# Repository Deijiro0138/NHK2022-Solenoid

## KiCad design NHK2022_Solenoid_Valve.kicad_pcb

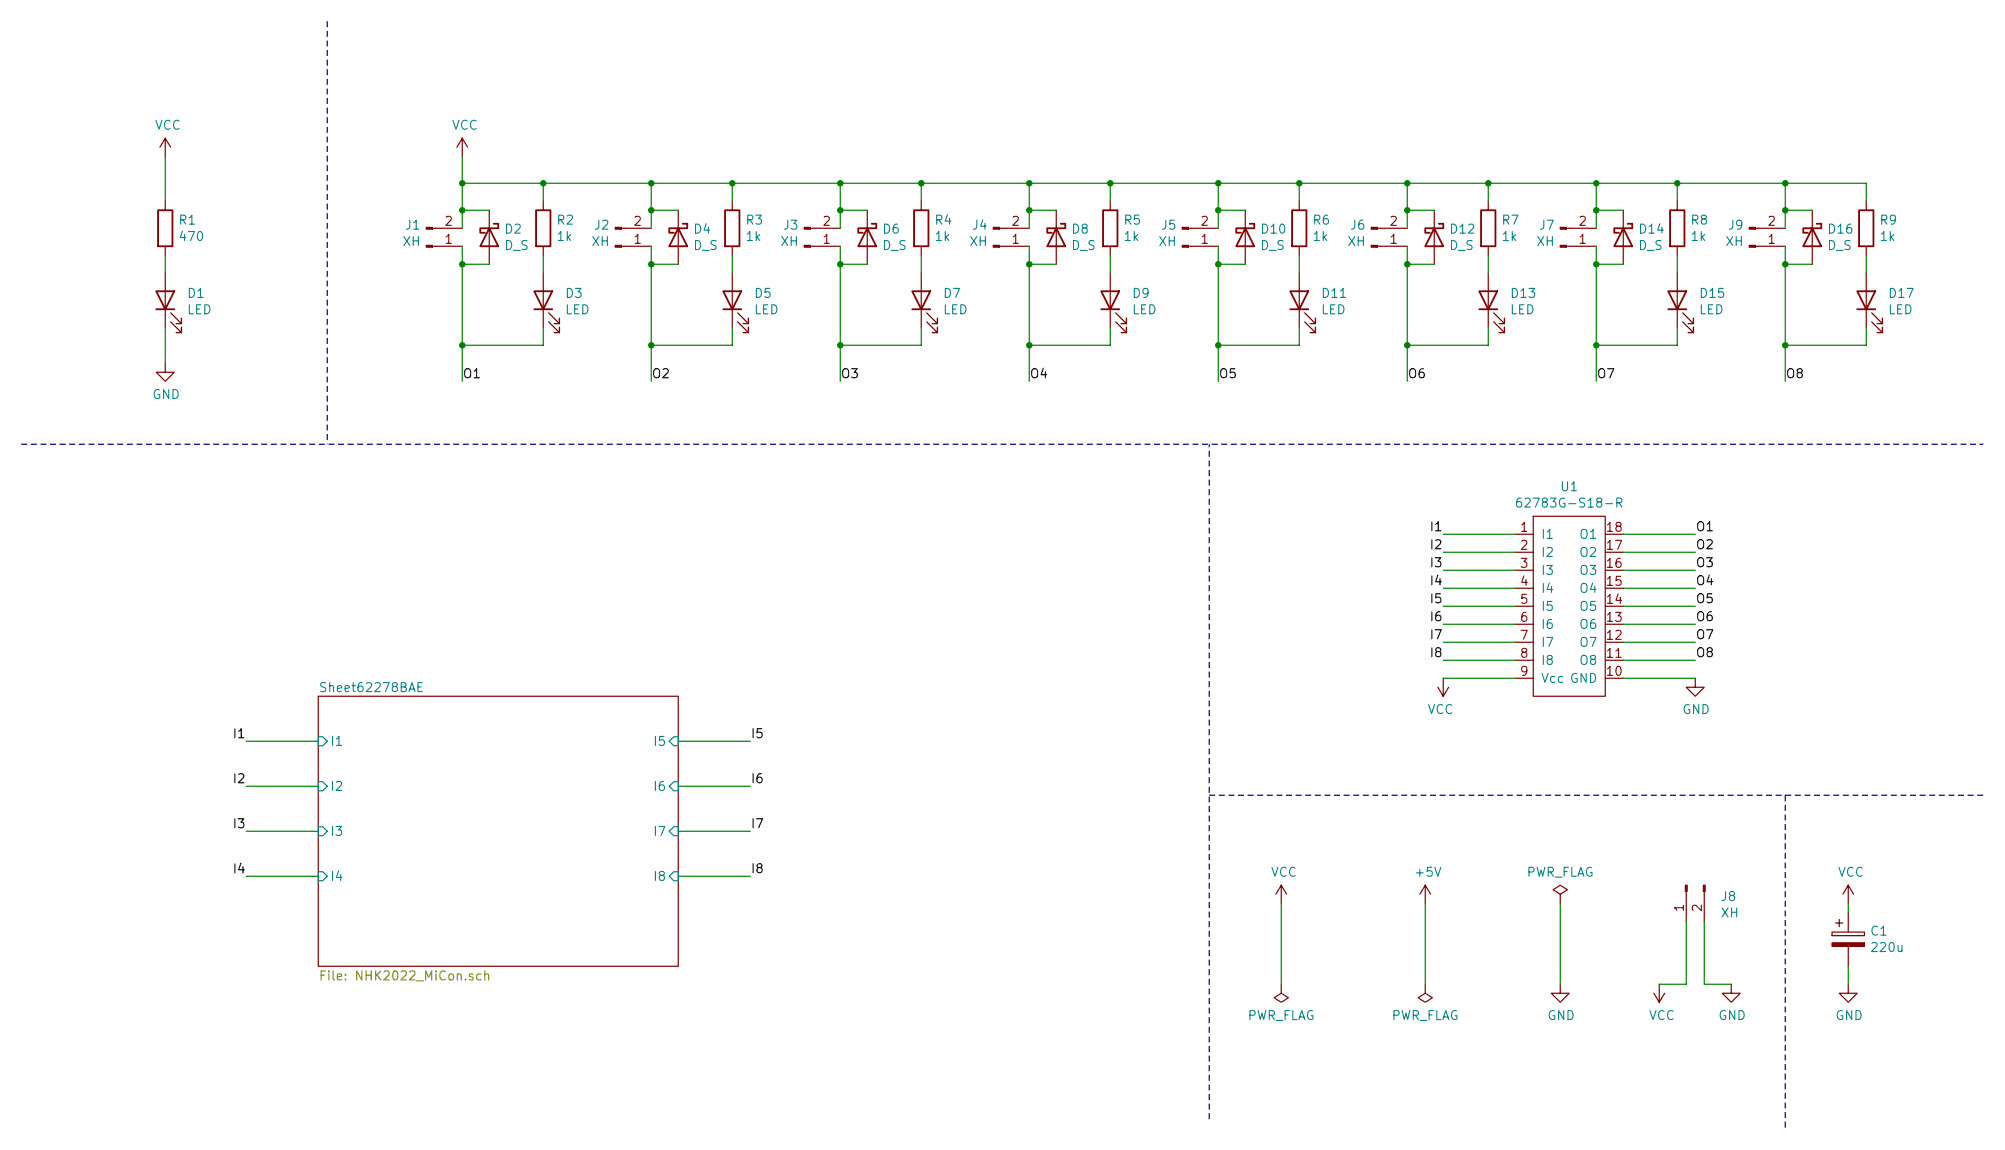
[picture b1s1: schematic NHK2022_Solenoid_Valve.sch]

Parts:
C1: 220u; CP_Radial_D8.0mm_P3.50mm
D1, D3, D5, D7, D9, D11, D13, D15, D17: LED; LED_0603_1608Metric
D2, D4, D6, D8, D10, D12, D14, D16: D_S; D_SOD-323_HandSoldering
J1, J2, J3, J4, J5, J6, J7, J8, J9: XH; JST_XH_S2B-XH-A_1x02_P2.50mm_Horizontal
R1: 470; R_0603_1608Metric
R2, R3, R4, R5, R6, R7, R8, R9: 1k; R_0603_1608Metric
U1: 62783G-S18-R; SOP-18_7x12.5mm_P1.27mm

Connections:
/I1: U1.1 (I1); also elsewhere on the board
/I2: U1.2 (I2); also elsewhere on the board
/I3: U1.3 (I3); also elsewhere on the board
/I4: U1.4 (I4); also elsewhere on the board
/I5: U1.5 (I5); also elsewhere on the board
/I6: U1.6 (I6); also elsewhere on the board
/I7: U1.7 (I7); also elsewhere on the board
/I8: U1.8 (I8); also elsewhere on the board
/O1: D2.2 (A), D3.1 (K), J1.1, U1.18 (O1)
/O2: D4.2 (A), D5.1 (K), J2.1, U1.17 (O2)
/O3: D6.2 (A), D7.1 (K), J3.1, U1.16 (O3)
/O4: D8.2 (A), D9.1 (K), J4.1, U1.15 (O4)
/O5: D10.2 (A), D11.1 (K), J5.1, U1.14 (O5)
/O6: D12.2 (A), D13.1 (K), J6.1, U1.13 (O6)
/O7: D14.2 (A), D15.1 (K), J7.1, U1.12 (O7)
/O8: D16.2 (A), D17.1 (K), J9.1, U1.11 (O8)
GND: C1.2, D1.1 (K), J8.2, U1.10 (GND); also elsewhere on the board
unnamed: D1.2 (A), R1.2
unnamed: D3.2 (A), R2.2
unnamed: D5.2 (A), R3.2
unnamed: D7.2 (A), R4.2
unnamed: D9.2 (A), R5.2
unnamed: D11.2 (A), R6.2
unnamed: D13.2 (A), R7.2
unnamed: D15.2 (A), R8.2
unnamed: D17.2 (A), R9.2
VCC: C1.1, D2.1 (K), D4.1 (K), D6.1 (K), D8.1 (K), D10.1 (K), D12.1 (K), D14.1 (K), D16.1 (K), J1.2, J2.2, J3.2, J4.2, J5.2, J6.2, J7.2, J8.1, J9.2, R1.1, R2.1, R3.1, R4.1, R5.1, R6.1, R7.1, R8.1, R9.1, U1.9 (Vcc)

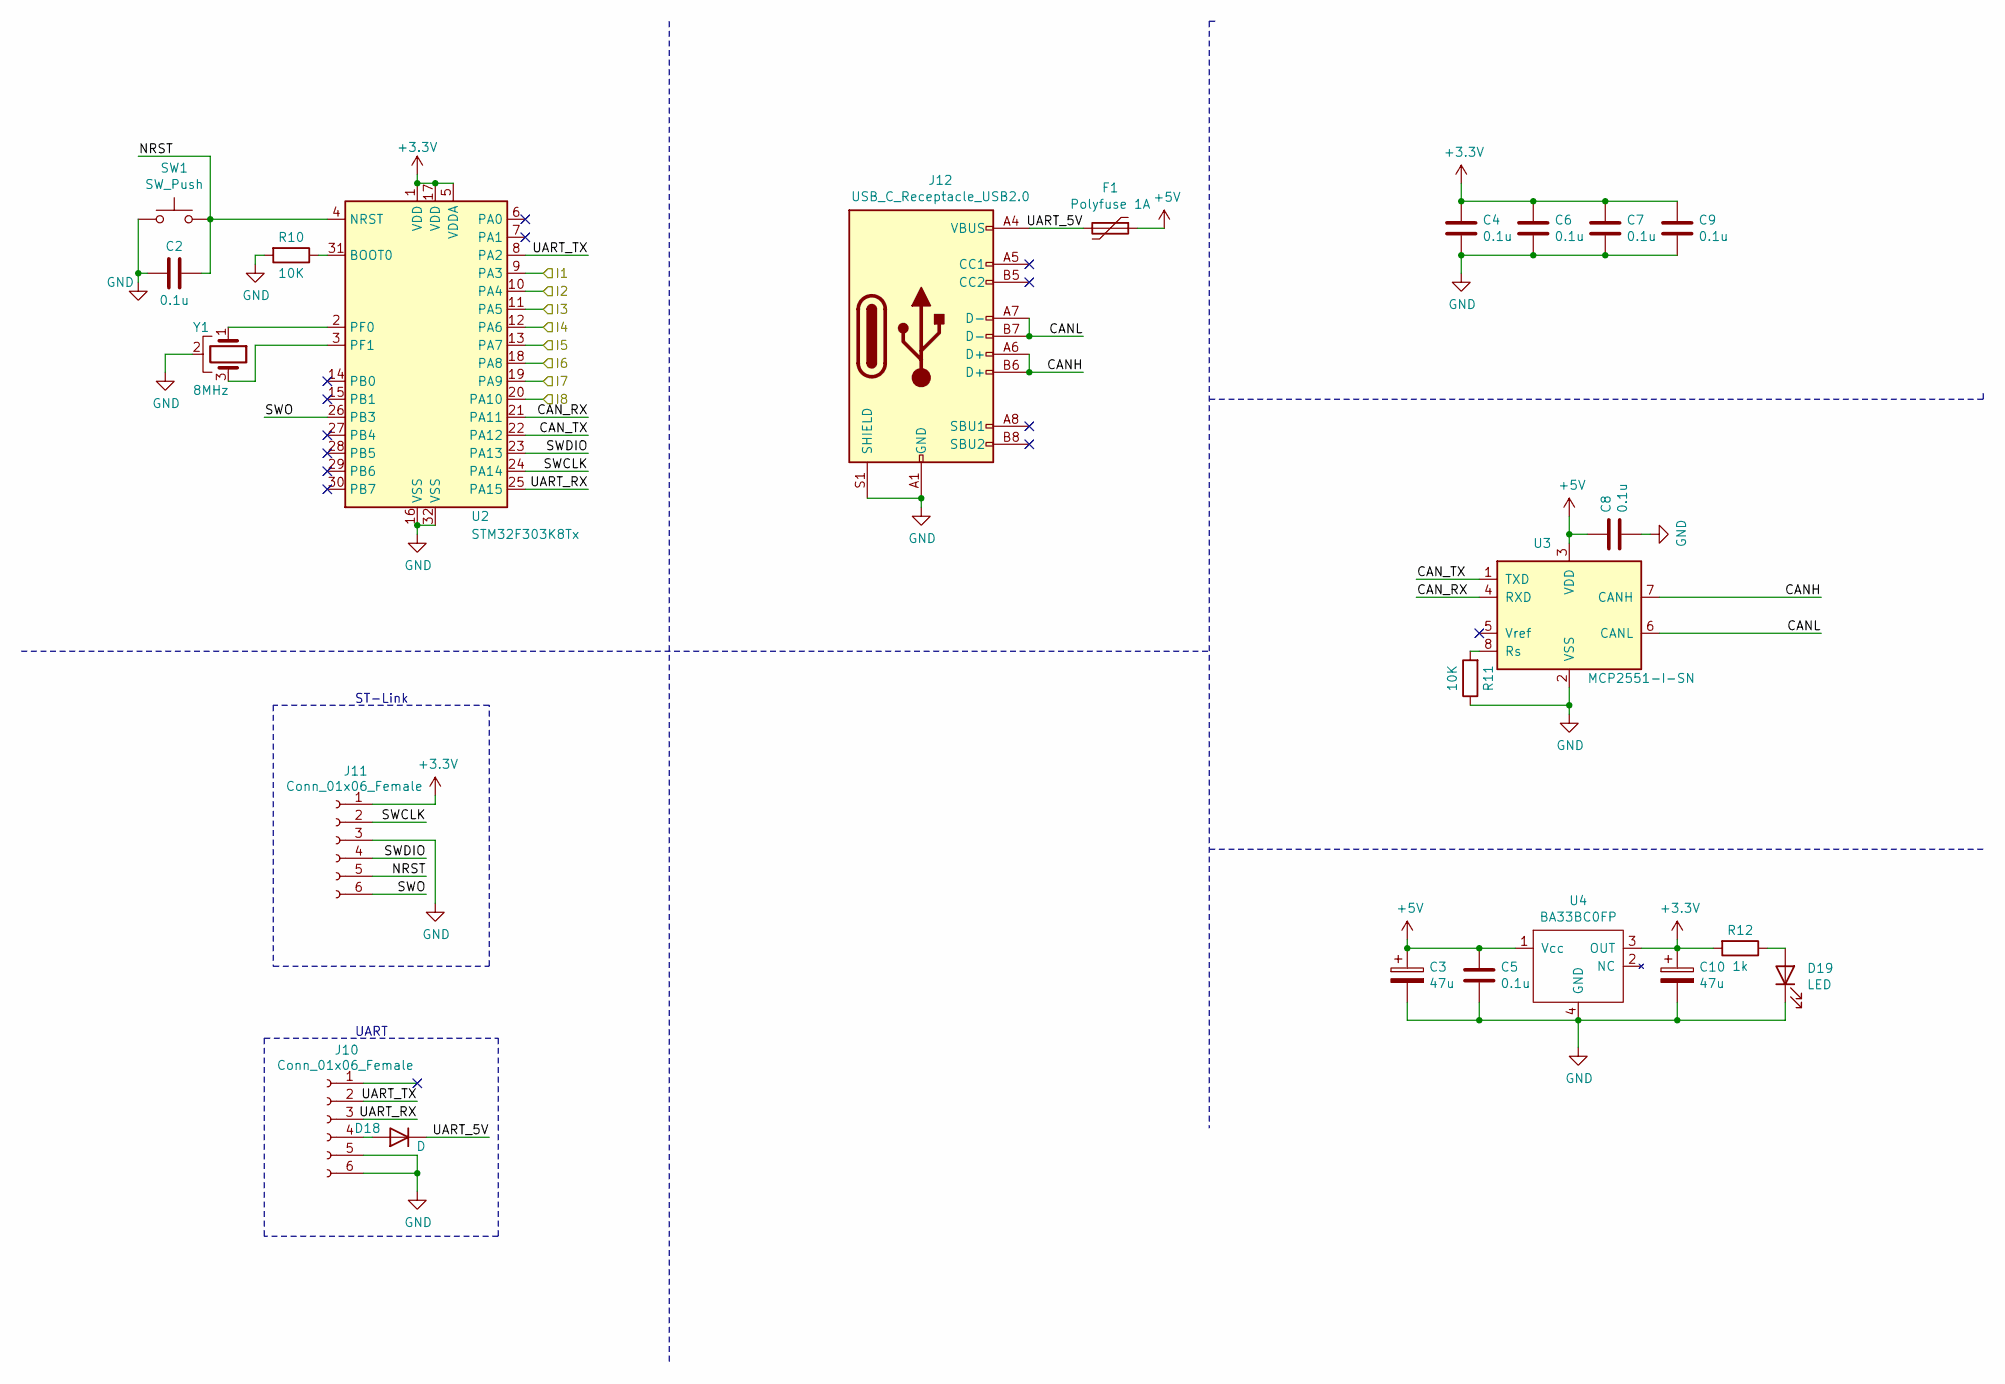
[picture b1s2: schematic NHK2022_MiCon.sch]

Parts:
C2, C4, C5, C6, C7, C8, C9: 0.1u; C_0603_1608Metric
C3, C10: 47u; CP_Radial_D6.3mm_P2.50mm
D18: D; D_SOD-123F
D19: LED; LED_0603_1608Metric
F1: Polyfuse 1A; Fuse_1812_4532Metric
J10, J11: Conn_01x06_Female; PinSocket_1x06_P2.54mm_Horizontal
J12: USB_C_Receptacle_USB2.0; USB_C_Receptacle_Palconn_UTC16-G
R10, R11: 10K; R_0603_1608Metric
R12: 1k; R_0603_1608Metric
SW1: SW_Push; SW_SPST_CK_RS282G05A3
U2: STM32F303K8Tx; LQFP-32_7x7mm_P0.8mm
U3: MCP2551-I-SN; SOIC-8_3.9x4.9mm_P1.27mm
U4: BA33BC0FP; TO-252-3_TabPin4
Y1: 8MHz; Resonator-3Pin_W8.0mm_H3.5mm

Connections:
+3V3: C4.1, C6.1, C7.1, C9.1, C10.1, J11.1, R12.2, U2.1 (VDD), U2.5 (VDDA), U2.17 (VDD), U4.3 (OUT); also elsewhere on the board
+5V: C3.1, C5.1, C8.1, F1.1, U3.3 (VDD), U4.1 (Vcc)
/I1: U2.9 (PA3); also elsewhere on the board
/I2: U2.10 (PA4); also elsewhere on the board
/I3: U2.11 (PA5); also elsewhere on the board
/I4: U2.12 (PA6); also elsewhere on the board
/I5: U2.13 (PA7); also elsewhere on the board
/I6: U2.18 (PA8); also elsewhere on the board
/I7: U2.19 (PA9); also elsewhere on the board
/I8: U2.20 (PA10); also elsewhere on the board
/Sheet62278BAE/CANH: J12.A6 (D+), J12.B6 (D+), U3.7 (CANH)
/Sheet62278BAE/CANL: J12.A7 (D-), J12.B7 (D-), U3.6 (CANL)
/Sheet62278BAE/CAN_RX: U2.21 (PA11), U3.4 (RXD)
/Sheet62278BAE/CAN_TX: U2.22 (PA12), U3.1 (TXD)
/Sheet62278BAE/NRST: C2.1, J11.5, SW1.2, U2.4 (NRST); also elsewhere on the board
/Sheet62278BAE/SWCLK: J11.2, U2.24 (PA14); also elsewhere on the board
/Sheet62278BAE/SWDIO: J11.4, U2.23 (PA13); also elsewhere on the board
/Sheet62278BAE/SWO: J11.6, U2.26 (PB3); also elsewhere on the board
/Sheet62278BAE/UART_5V: D18.1 (K), F1.2, J12.A4 (VBUS), J12.A9 (VBUS), J12.B4 (VBUS), J12.B9 (VBUS)
/Sheet62278BAE/UART_RX: J10.3, U2.25 (PA15); also elsewhere on the board
/Sheet62278BAE/UART_TX: J10.2, U2.8 (PA2); also elsewhere on the board
GND: C2.2, C3.2, C4.2, C5.2, C6.2, C7.2, C8.2, C9.2, C10.2, D19.1 (K), J10.5, J10.6, J11.3, J12.A1 (GND), J12.A12 (GND), J12.B1 (GND), J12.B12 (GND), J12.S1 (SHIELD), R10.2, R11.1, SW1.1, U2.16 (VSS), U2.32 (VSS), U3.2 (VSS), U4.4 (GND), Y1.2; also elsewhere on the board
unnamed 39: D18.2 (A), J10.4; also elsewhere on the board
unnamed: D19.2 (A), R12.1
unnamed: R10.1, U2.31 (BOOT0)
unnamed: R11.2, U3.8 (Rs)
unnamed: U2.2 (PF0), Y1.1
unnamed: U2.3 (PF1), Y1.3

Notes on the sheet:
ST-Link
UART

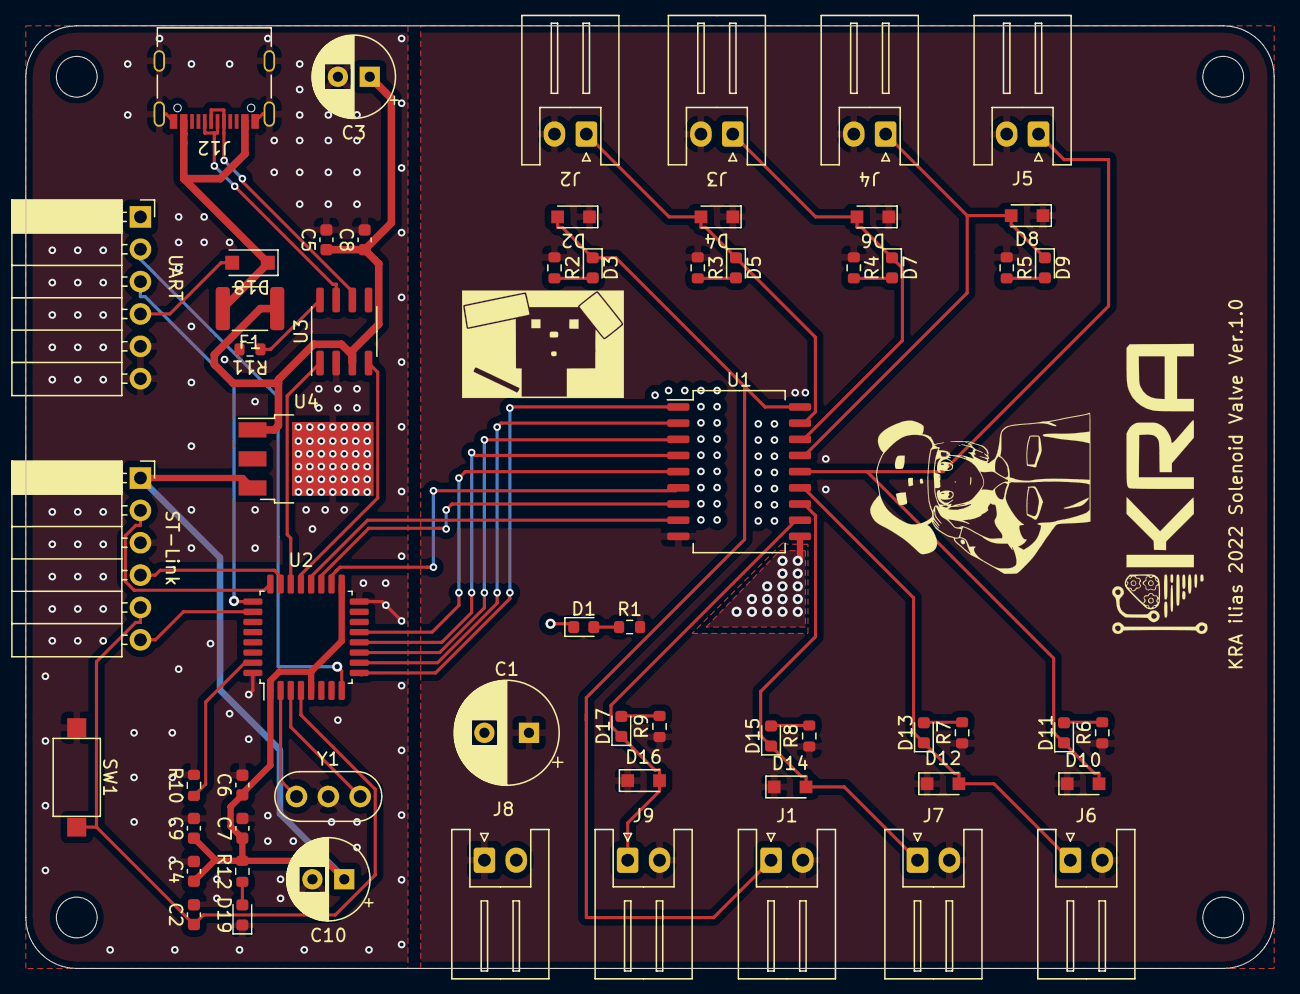
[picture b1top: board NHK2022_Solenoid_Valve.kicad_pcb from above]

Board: 2 copper layers, 98.0 x 74.0 mm, 67 parts (0 on the bottom side), 46 nets.

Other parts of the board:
G1: LOGO; rogi_bijo
G2: LOGO; kra_mono_a
G3: LOGO; rogi_inu_a
REF1, REF2, REF3, REF4: MountingHole_3.2mm_M3
ST-Link: Conn_01x06_Female; PinSocket_1x06_P2.54mm_Horizontal
UART: Conn_01x06_Female; PinSocket_1x06_P2.54mm_Horizontal

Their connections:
+3V3: ST-Link.1; also elsewhere on the board
/Sheet62278BAE/NRST: ST-Link.5; also elsewhere on the board
/Sheet62278BAE/SWCLK: ST-Link.2; also elsewhere on the board
/Sheet62278BAE/SWDIO: ST-Link.4; also elsewhere on the board
/Sheet62278BAE/SWO: ST-Link.6; also elsewhere on the board
/Sheet62278BAE/UART_RX: UART.3; also elsewhere on the board
/Sheet62278BAE/UART_TX: UART.2; also elsewhere on the board
GND: ST-Link.3, UART.5, UART.6; also elsewhere on the board
unnamed 39: UART.4; also elsewhere on the board
